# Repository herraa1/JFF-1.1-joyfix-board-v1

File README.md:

# JFF Revision 1.1 JoyFix Board

This is an interposer board that fixes the existing bug in the joystick circuit of the [Just For Fun (JFF) computer revision 1.1](https://github.com/konkotgit/JFF) (up to revision 1.1b) by @skoti.

See the [Omega 1.4 Joyfix Board](https://github.com/herraa1/omega-1.4-joyfix-board-v1) for information on a similar (but not the same) bug affecting the [Omega Home Computer mainboard revision 1.4](https://github.com/skiselev/omega) by Sergey Kiselev.

> [!NOTE]
> This fix is not needed for [JFF 1.1c](https://github.com/konkotgit/JFF?tab=readme-ov-file#revisions), which includes the joystick circuit fix as per [#3](https://github.com/konkotgit/JFF/issues/3).

# The standard MSX joystick circuit

Please, refer to the [details about the standard MSX joystick circuit](https://github.com/herraa1/omega-1.4-joyfix-board-v1?tab=readme-ov-file#the-standard-msx-joystick-circuit) in the [Omega 1.4 Joyfix Board](https://github.com/herraa1/omega-1.4-joyfix-board-v1).

Focusing on the relevant information, output trigger signals must be connected via open-collector buffers like this:
- :white_check_mark: the output at the open-collector buffer corresponding to signal IOB0 is connected to joystick port 1 trigger A
- :white_check_mark: the output at the open-collector buffer corresponding to signal IOB1 is connected to joystick port 1 trigger B
- :white_check_mark: the output at the open-collector buffer corresponding to signal IOB2 is connected to joystick port 2 trigger A
- :white_check_mark: the output at the open-collector buffer corresponding to signal IOB3 is connected to joystick port 2 trigger B

# The JFF 1.1 joystick circuit

As can be seen on the depicted diagram, the JFF PSG circuit tries to mimic the standard MSX joystick circuit, but mixes up the output signals after the open-collector buffers.

If we look closely at the connection of the trigger output signals to the open-collector buffer inputs and the connection of the open-collector buffer outputs to the joystick port signals we can see that:
- :x: the output of the open-collector buffer corresponding to signal IOB0 is incorrectly connected to joystick port 2 trigger B (J2_TR2)
- :x: the output of the open-collector buffer corresponding to signal IOB1 is incorrectly connected to joystick port 2 trigger A (J2_TR1)
- :x: the output of the open-collector buffer corresponding to signal IOB2 is incorrectly connected to joystick port 1 trigger B (J1_TR2)
- :x: the output of the open-collector buffer corresponding to signal IOB3 is incorrectly connected to joystick port 1 trigger A (J1_TR1)

# The fix

The circuit can be easily fixed by re-routing the affected signals to make them available at the right place.

In the JFF 1.1 joystick circuit we have the following connections related to the triggers, taking into account the functional pinout of the [74LS07](https://www.ti.com/lit/ds/symlink/sn74ls07.pdf):
- input `Pin 1` of U20 (connected to IOB0) outputs to `Pin 2` of U20 (incorrectly connected to joystick port 2 trigger B, aka J2_TR2)
- input `Pin 3` of U20 (connected to IOB1) outputs to `Pin 4` of U20 (incorrectly connected to joystick port 2 trigger A, aka J2_TR1)
- input `Pin 5` of U20 (connected to IOB2) outputs to `Pin 6` of U20 (incorrectly connected to joystick port 1 trigger B, aka J1_TR2)
- input `Pin 9` of U20 (connected to IOB3) outputs to `Pin 8` of U20 (incorrectly connected to joystick port 1 trigger A, aka J1_TR1)

A clean and easy approach to fix the circuit is to use an interposer board at U20 (74LS07 open-collector buffer) that performs the needed re-mapping of signals.

So to re-route the signals to match the MSX standard joystick circuit we can map the U20-original signals to a new set of U20-interposed signals (where the 74LS07 will be actually connected), like this:
- Connect `Pin 2 of U20-interposed` (buffered output of Pin 1 of U20-interposed which connects to IOB0) to `Pin 8 of U20-original` (connected to joystick port 1 trigger A, aka J1_TR1), so that Pin 1 of U20-original (IOB0) outputs to Pin 8 of U20-original (joystick port 1 trigger A) ( `violet` path on the diagram)
- Connect `Pin 4 of U20-interposed` (buffered output of Pin 3 of U20-interposed which connects to IOB1) to `Pin 6 of U20-original` (connected to joystick port 1 trigger B, aka J1_TR2), so that Pin 3 of U20-original (IOB1) outputs to Pin 6 of U20-original (joystick port 1 trigger B) ( `green` path on the diagram)
- Connect `Pin 6 of U20-interposed` (buffered output of Pin 5 of U20-interposed which connects to IOB2) to `Pin 4 of U20-original` (connected to joystick port 2 trigger A, aka J2_TR1), so that Pin 5 of U20-original (IOB2) outputs to Pin 4 of U20-original (joystick port 2 trigger A) ( `yellow` path on the diagram)
- Connect `Pin 8 of U20-interposed` (buffered output of Pin 9 of U20-interposed which connects to IOB3) to `Pin 2 of U20-original` (connected to joystick port 2 trigger B, aka J2_TR2), so that Pin 9 of U20-original (IOB3) outputs to Pin 2 of U20-original (joystick port 2 trigger B) ( `orange` path on the diagram)
- Connect all other Pins of U20-interposed to the same Pins of U20-original (i.e Pin 1 to Pin 1, Pin 3 to Pin 3, etc.) ( solid `pink` paths on the diagram)

Summarizing, after the re-routing we have fixed the issue:
- `Pin 1 of U20-original` (connected to IOB0) outputs to `Pin 8 of U20-original` (connected to joystick port 1 trigger A)
- `Pin 3 of U20-original` (connected to IOB1) outputs to `Pin 6 of U20-original` (connected to joystick port 1 trigger B)
- `Pin 5 of U20-original` (connected to IOB2) outputs to `Pin 4 of U20-original` (connected to joystick port 2 trigger A)
- `Pin 9 of U20-original` (connected to IOB3) outputs to `Pin 2 of U20-original` (connected to joystick port 2 trigger B)

And the complete trigger connection diagram matches now the original MSX joystick circuit diagram:
- :white_check_mark: the output at the open-collector buffer corresponding to signal IOB0 is connected to joystick port 1 trigger A (J1_TR1)
- :white_check_mark: the output at the open-collector buffer corresponding to signal IOB1 is connected to joystick port 1 trigger B (J1_TR2)
- :white_check_mark: the output at the open-collector buffer corresponding to signal IOB2 is connected to joystick port 2 trigger A (J2_TR1)
- :white_check_mark: the output at the open-collector buffer corresponding to signal IOB3 is connected to joystick port 2 trigger B (J2_TR2)

# Hardware

## [JFF-joyfix-board-v1-Build1](hardware/kicad/JFF-joyfix-board-v1-Build1/)

:white_check_mark: This board has been successfully built and tested.

[Bill Of Materials (BoM)](https://htmlpreview.github.io/?https://raw.githubusercontent.com/herraa1/JFF-1.1-joyfix-board-v1/main/hardware/kicad/JFF-joyfix-board-v1-Build1/bom/ibom.html)

[Schematic and PCB](https://kicanvas.org/?github=https%3A%2F%2Fgithub.com%2Fherraa1%2FJFF-1.1-joyfix-board-v1%2Ftree%2Fmain%2Fhardware%2Fkicad%2FJFF-joyfix-board-v1-Build1)

## PCB Manufacturing tips

As the joyfix board is super small, some PCB manufacturers may make extra charges when building standalone prototypes or panelizing the boards using v-cuts.

One way to avoid the extra costs is panelizing the joyfix board using "mouse bites".

# Build instructions

Please, follow the [Omega 1.4 Joyfix Board Build Instructions](https://github.com/herraa1/omega-1.4-joyfix-board-v1?tab=readme-ov-file#build-instructions) to assemble the joyfix board. Both boards are assembled using the same procedure.

# Installation instructions

## Step by step instructions

1. Locate the U20 74LS07 IC chip on the JFF computer.

It is a DIP14 IC available near the joystick port 1.

2. Remove the 74LS07 chip from the U20 socket, insert it into the joyfix board socket, and then insert the joyfix board into the U20 socket.

Respect the IC notch markings when orienting both the 74LS07 and the joyfix board for insertion.

Make sure you properly align the joyfix board header pins to the U20 socket to make a good insertion without damaging the U20 socket.

# Validating the fix

Please, refer to the the Omega 1.4 Joyfix Board [Validating the fix](https://github.com/herraa1/omega-1.4-joyfix-board-v1?tab=readme-ov-file#validating-the-fix) section for additional details on how to validate the joyfix board using [MSXJIO](https://github.com/louthrax/MSXJIO) by @Louthrax.

## JFF 1.1 with the joyfix board

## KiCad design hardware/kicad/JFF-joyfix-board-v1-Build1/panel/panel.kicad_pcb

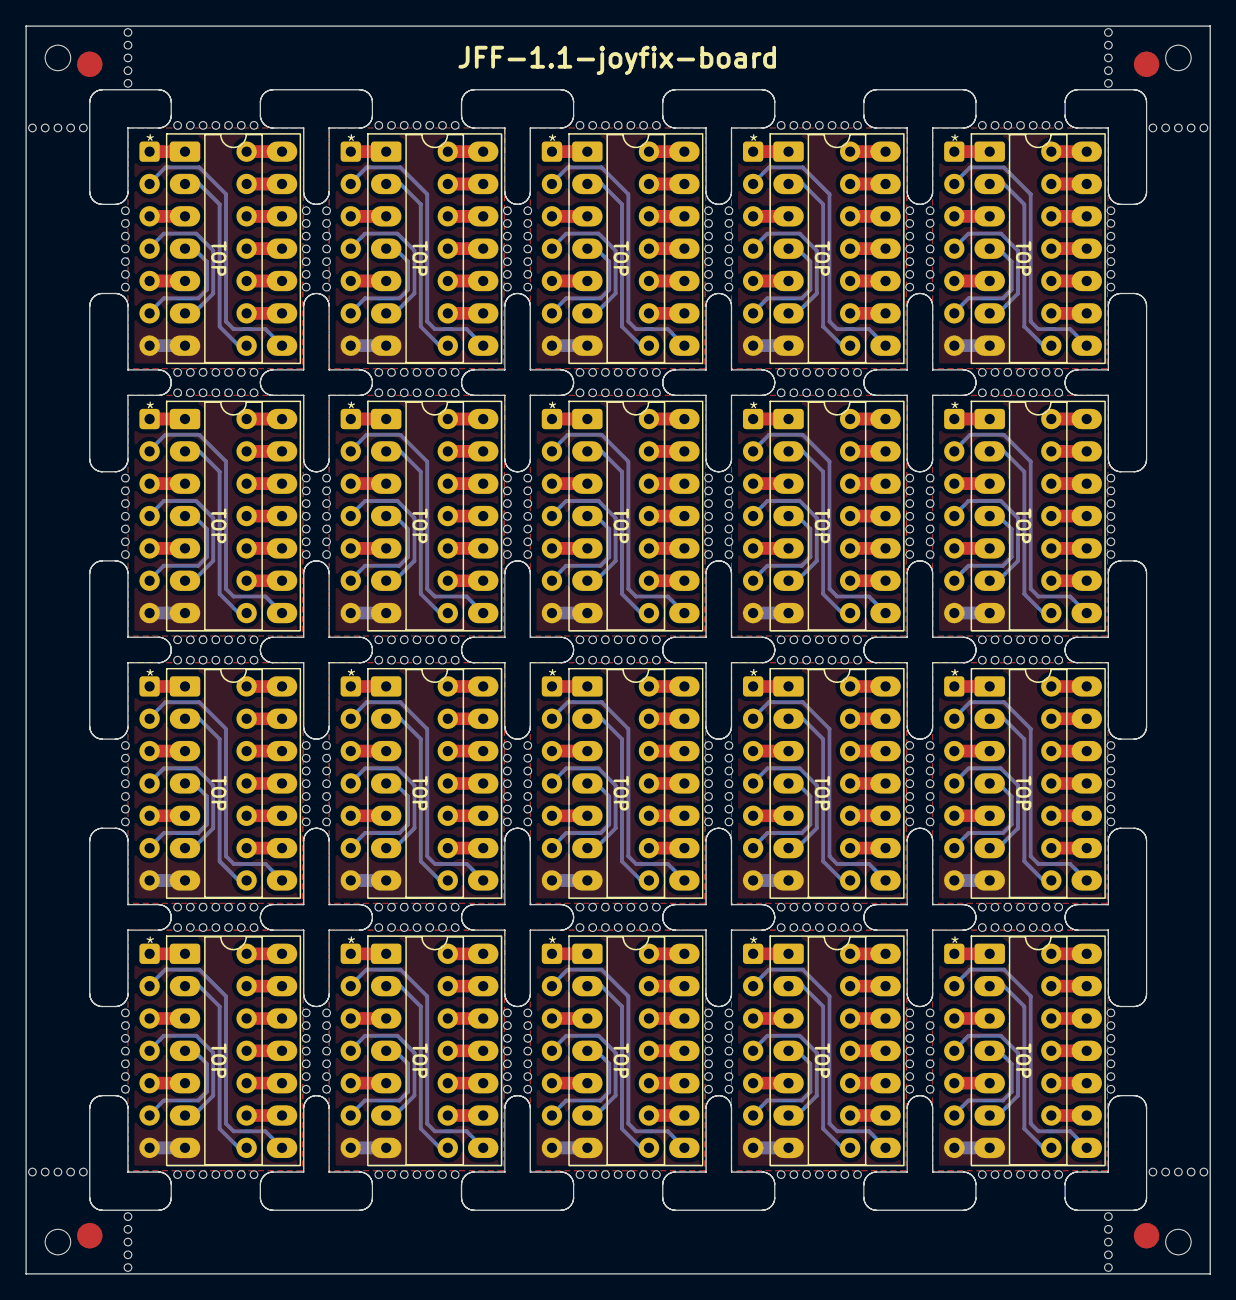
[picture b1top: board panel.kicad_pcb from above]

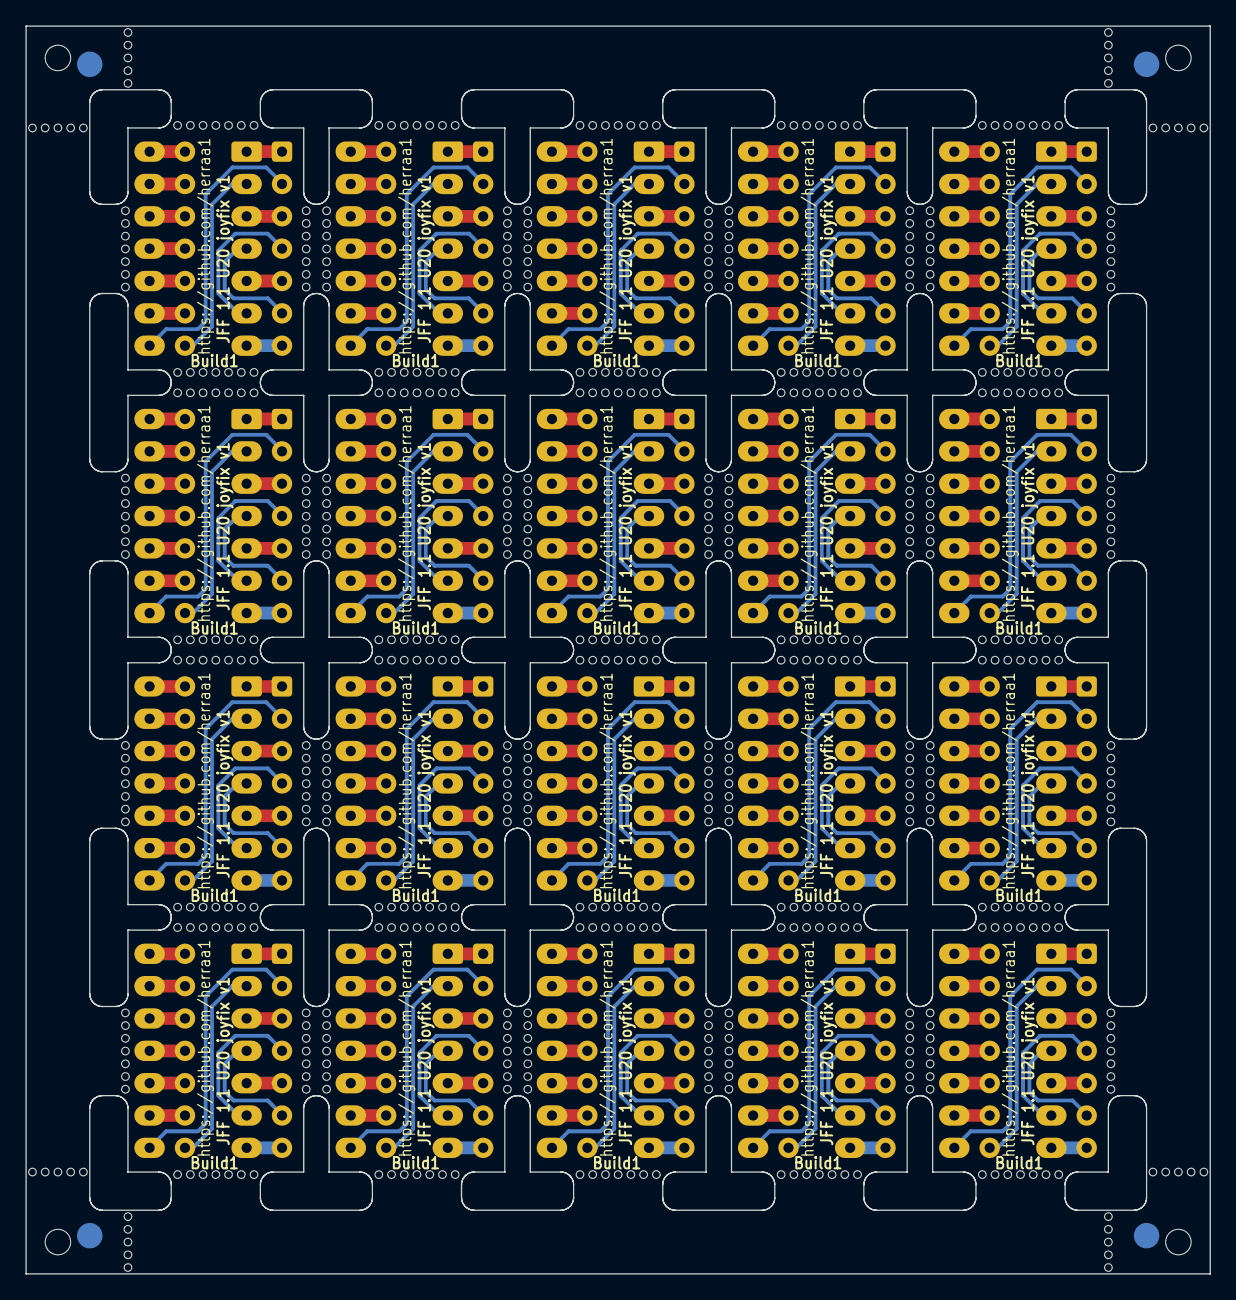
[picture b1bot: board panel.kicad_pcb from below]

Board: 2 copper layers, 93.0 x 98.0 mm, 652 parts (4 on the bottom side), 280 nets.

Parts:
J1, J1#2, J1#3, J1#4, J1#5, J1#6, J1#7, J1#8, J1#9, J1#10, J1#11, J1#12, J1#13, J1#14, J1#15, J1#16, J1#17, J1#18, J1#19, J1#20: To Motherboard; DIP-14_W7.62mm_Socket_Custom
J2, J2#2, J2#3, J2#4, J2#5, J2#6, J2#7, J2#8, J2#9, J2#10, J2#11, J2#12, J2#13, J2#14, J2#15, J2#16, J2#17, J2#18, J2#19, J2#20: To 74LS07; DIP-14_W7.62mm_Socket_LongPads
KiKit_FID_B_1, KiKit_FID_B_2, KiKit_FID_B_3, KiKit_FID_B_4: Fiducial
KiKit_FID_T_1, KiKit_FID_T_2, KiKit_FID_T_3, KiKit_FID_T_4: Fiducial
KiKit_MB_1_2, KiKit_MB_1_3, KiKit_MB_1_4, KiKit_MB_1_5, KiKit_MB_1_6, KiKit_MB_1_7, KiKit_MB_1_8, KiKit_MB_2_2, KiKit_MB_2_3, KiKit_MB_2_4, KiKit_MB_2_5, KiKit_MB_2_6, KiKit_MB_2_7, KiKit_MB_2_8, KiKit_MB_3_2, KiKit_MB_3_3, KiKit_MB_3_4, KiKit_MB_3_5, KiKit_MB_3_6, KiKit_MB_3_7, KiKit_MB_3_8, KiKit_MB_4_2, KiKit_MB_4_3, KiKit_MB_4_4, KiKit_MB_4_5, KiKit_MB_4_6, KiKit_MB_4_7, KiKit_MB_4_8, KiKit_MB_5_2, KiKit_MB_5_3, KiKit_MB_5_4, KiKit_MB_5_5, KiKit_MB_5_6, KiKit_MB_5_7, KiKit_MB_5_8, KiKit_MB_6_2, KiKit_MB_6_3, KiKit_MB_6_4, KiKit_MB_6_5, KiKit_MB_6_6, KiKit_MB_6_7, KiKit_MB_6_8, KiKit_MB_7_2, KiKit_MB_7_3, KiKit_MB_7_4, KiKit_MB_7_5, KiKit_MB_7_6, KiKit_MB_7_7, KiKit_MB_7_8, KiKit_MB_8_2, KiKit_MB_8_3, KiKit_MB_8_4, KiKit_MB_8_5, KiKit_MB_8_6, KiKit_MB_8_7, KiKit_MB_8_8, KiKit_MB_9_2, KiKit_MB_9_3, KiKit_MB_9_4, KiKit_MB_9_5, KiKit_MB_9_6, KiKit_MB_9_7, KiKit_MB_9_8, KiKit_MB_10_2, KiKit_MB_10_3, KiKit_MB_10_4, KiKit_MB_10_5, KiKit_MB_10_6, KiKit_MB_10_7, KiKit_MB_10_8, KiKit_MB_11_2, KiKit_MB_11_3, KiKit_MB_11_4, KiKit_MB_11_5, KiKit_MB_11_6, KiKit_MB_11_7, KiKit_MB_11_8, KiKit_MB_12_2, KiKit_MB_12_3, KiKit_MB_12_4, KiKit_MB_12_5, KiKit_MB_12_6, KiKit_MB_12_7, KiKit_MB_12_8, KiKit_MB_13_2, KiKit_MB_13_3, KiKit_MB_13_4, KiKit_MB_13_5, KiKit_MB_13_6, KiKit_MB_13_7, KiKit_MB_13_8, KiKit_MB_14_2, KiKit_MB_14_3, KiKit_MB_14_4, KiKit_MB_14_5, KiKit_MB_14_6, KiKit_MB_14_7, KiKit_MB_14_8, KiKit_MB_15_2, KiKit_MB_15_3, KiKit_MB_15_4, KiKit_MB_15_5, KiKit_MB_15_6, KiKit_MB_15_7, KiKit_MB_15_8, KiKit_MB_16_2, KiKit_MB_16_3, KiKit_MB_16_4, KiKit_MB_16_5, KiKit_MB_16_6, KiKit_MB_16_7, KiKit_MB_16_8, KiKit_MB_17_2, KiKit_MB_17_3, KiKit_MB_17_4, KiKit_MB_17_5, KiKit_MB_17_6, KiKit_MB_17_7, KiKit_MB_17_8, KiKit_MB_18_2, KiKit_MB_18_3, KiKit_MB_18_4, KiKit_MB_18_5, KiKit_MB_18_6, KiKit_MB_18_7, KiKit_MB_18_8, KiKit_MB_19_2, KiKit_MB_19_3, KiKit_MB_19_4, KiKit_MB_19_5, KiKit_MB_19_6, KiKit_MB_19_7, KiKit_MB_19_8, KiKit_MB_20_2, KiKit_MB_20_3, KiKit_MB_20_4, KiKit_MB_20_5, KiKit_MB_20_6, KiKit_MB_20_7, KiKit_MB_20_8, KiKit_MB_21_2, KiKit_MB_21_3, KiKit_MB_21_4, KiKit_MB_21_5, KiKit_MB_21_6, KiKit_MB_21_7, KiKit_MB_21_8, KiKit_MB_22_2, KiKit_MB_22_3, KiKit_MB_22_4, KiKit_MB_22_5, KiKit_MB_22_6, KiKit_MB_22_7, KiKit_MB_22_8, KiKit_MB_23_2, KiKit_MB_23_3, KiKit_MB_23_4, KiKit_MB_23_5, KiKit_MB_23_6, KiKit_MB_23_7, KiKit_MB_23_8, KiKit_MB_24_2, KiKit_MB_24_3, KiKit_MB_24_4, KiKit_MB_24_5, KiKit_MB_24_6, KiKit_MB_24_7, KiKit_MB_24_8, KiKit_MB_25_2, KiKit_MB_25_3, KiKit_MB_25_4, KiKit_MB_25_5, KiKit_MB_25_6, KiKit_MB_25_7, KiKit_MB_25_8, KiKit_MB_26_2, KiKit_MB_26_3, KiKit_MB_26_4, KiKit_MB_26_5, KiKit_MB_26_6, KiKit_MB_26_7, KiKit_MB_26_8, KiKit_MB_27_2, KiKit_MB_27_3, KiKit_MB_27_4, KiKit_MB_27_5, KiKit_MB_27_6, KiKit_MB_27_7, KiKit_MB_27_8, KiKit_MB_28_2, KiKit_MB_28_3, KiKit_MB_28_4, KiKit_MB_28_5, KiKit_MB_28_6, KiKit_MB_28_7, KiKit_MB_28_8, KiKit_MB_29_2, KiKit_MB_29_3, KiKit_MB_29_4, KiKit_MB_29_5, KiKit_MB_29_6, KiKit_MB_29_7, KiKit_MB_29_8, KiKit_MB_30_2, KiKit_MB_30_3, KiKit_MB_30_4, KiKit_MB_30_5, KiKit_MB_30_6, KiKit_MB_30_7, KiKit_MB_30_8, KiKit_MB_31_2, KiKit_MB_31_3, KiKit_MB_31_4, KiKit_MB_31_5, KiKit_MB_31_6, KiKit_MB_31_7, KiKit_MB_31_8, KiKit_MB_32_2, KiKit_MB_32_3, KiKit_MB_32_4, KiKit_MB_32_5, KiKit_MB_32_6, KiKit_MB_32_7, KiKit_MB_32_8, KiKit_MB_33_2, KiKit_MB_33_3, KiKit_MB_33_4, KiKit_MB_33_5, KiKit_MB_33_6, KiKit_MB_33_7, KiKit_MB_33_8, KiKit_MB_34_2, KiKit_MB_34_3, KiKit_MB_34_4, KiKit_MB_34_5, KiKit_MB_34_6, KiKit_MB_34_7, KiKit_MB_34_8, KiKit_MB_35_2, KiKit_MB_35_3, KiKit_MB_35_4, KiKit_MB_35_5, KiKit_MB_35_6, KiKit_MB_35_7, KiKit_MB_35_8, KiKit_MB_36_2, KiKit_MB_36_3, KiKit_MB_36_4, KiKit_MB_36_5, KiKit_MB_36_6, KiKit_MB_36_7, KiKit_MB_36_8, KiKit_MB_37_2, KiKit_MB_37_3, KiKit_MB_37_4, KiKit_MB_37_5, KiKit_MB_37_6, KiKit_MB_37_7, KiKit_MB_37_8, KiKit_MB_38_2, KiKit_MB_38_3, KiKit_MB_38_4, KiKit_MB_38_5, KiKit_MB_38_6, KiKit_MB_38_7, KiKit_MB_38_8, KiKit_MB_39_2, KiKit_MB_39_3, KiKit_MB_39_4, KiKit_MB_39_5, KiKit_MB_39_6, KiKit_MB_39_7, KiKit_MB_39_8, KiKit_MB_40_2, KiKit_MB_40_3, KiKit_MB_40_4, KiKit_MB_40_5, KiKit_MB_40_6, KiKit_MB_40_7, KiKit_MB_40_8, KiKit_MB_41_2, KiKit_MB_41_3, KiKit_MB_41_4, KiKit_MB_41_5, KiKit_MB_41_6, KiKit_MB_41_7, KiKit_MB_41_8, KiKit_MB_42_2, KiKit_MB_42_3, KiKit_MB_42_4, KiKit_MB_42_5, KiKit_MB_42_6, KiKit_MB_42_7, KiKit_MB_42_8, KiKit_MB_43_2, KiKit_MB_43_3, KiKit_MB_43_4, KiKit_MB_43_5, KiKit_MB_43_6, KiKit_MB_43_7, KiKit_MB_43_8, KiKit_MB_44_2, KiKit_MB_44_3, KiKit_MB_44_4, KiKit_MB_44_5, KiKit_MB_44_6, KiKit_MB_44_7, KiKit_MB_44_8, KiKit_MB_45_2, KiKit_MB_45_3, KiKit_MB_45_4, KiKit_MB_45_5, KiKit_MB_45_6, KiKit_MB_45_7, KiKit_MB_45_8, KiKit_MB_46_2, KiKit_MB_46_3, KiKit_MB_46_4, KiKit_MB_46_5, KiKit_MB_46_6, KiKit_MB_46_7, KiKit_MB_46_8, KiKit_MB_47_2, KiKit_MB_47_3, KiKit_MB_47_4, KiKit_MB_47_5, KiKit_MB_47_6, KiKit_MB_47_7, KiKit_MB_47_8, KiKit_MB_48_2, KiKit_MB_48_3, KiKit_MB_48_4, KiKit_MB_48_5, KiKit_MB_48_6, KiKit_MB_48_7, KiKit_MB_48_8, KiKit_MB_49_2, KiKit_MB_49_3, KiKit_MB_49_4, KiKit_MB_49_5, KiKit_MB_49_6, KiKit_MB_49_7, KiKit_MB_49_8, KiKit_MB_50_2, KiKit_MB_50_3, KiKit_MB_50_4, KiKit_MB_50_5, KiKit_MB_50_6, KiKit_MB_50_7, KiKit_MB_50_8, KiKit_MB_51_2, KiKit_MB_51_3, KiKit_MB_51_4, KiKit_MB_51_5, KiKit_MB_51_6, KiKit_MB_51_7, KiKit_MB_51_8, KiKit_MB_52_2, KiKit_MB_52_3, KiKit_MB_52_4, KiKit_MB_52_5, KiKit_MB_52_6, KiKit_MB_52_7, KiKit_MB_52_8, KiKit_MB_53_2, KiKit_MB_53_3, KiKit_MB_53_4, KiKit_MB_53_5, KiKit_MB_53_6, KiKit_MB_53_7, KiKit_MB_53_8, KiKit_MB_54_2, KiKit_MB_54_3, KiKit_MB_54_4, KiKit_MB_54_5, KiKit_MB_54_6, KiKit_MB_54_7, KiKit_MB_54_8, KiKit_MB_55_2, KiKit_MB_55_3, KiKit_MB_55_4, KiKit_MB_55_5, KiKit_MB_55_6, KiKit_MB_55_7, KiKit_MB_55_8, KiKit_MB_56_2, KiKit_MB_56_3, KiKit_MB_56_4, KiKit_MB_56_5, KiKit_MB_56_6, KiKit_MB_56_7, KiKit_MB_56_8, KiKit_MB_57_2, KiKit_MB_57_3, KiKit_MB_57_4, KiKit_MB_57_5, KiKit_MB_57_6, KiKit_MB_57_7, KiKit_MB_57_8, KiKit_MB_58_2, KiKit_MB_58_3, KiKit_MB_58_4, KiKit_MB_58_5, KiKit_MB_58_6, KiKit_MB_58_7, KiKit_MB_58_8, KiKit_MB_59_2, KiKit_MB_59_3, KiKit_MB_59_4, KiKit_MB_59_5, KiKit_MB_59_6, KiKit_MB_59_7, KiKit_MB_59_8, KiKit_MB_60_2, KiKit_MB_60_3, KiKit_MB_60_4, KiKit_MB_60_5, KiKit_MB_60_6, KiKit_MB_60_7, KiKit_MB_60_8, KiKit_MB_61_2, KiKit_MB_61_3, KiKit_MB_61_4, KiKit_MB_61_5, KiKit_MB_61_6, KiKit_MB_61_7, KiKit_MB_61_8, KiKit_MB_62_2, KiKit_MB_62_3, KiKit_MB_62_4, KiKit_MB_62_5, KiKit_MB_62_6, KiKit_MB_62_7, KiKit_MB_62_8, KiKit_MB_63_2, KiKit_MB_63_3, KiKit_MB_63_4, KiKit_MB_63_5, KiKit_MB_63_6, KiKit_MB_63_7, KiKit_MB_63_8, KiKit_MB_64_2, KiKit_MB_64_3, KiKit_MB_64_4, KiKit_MB_64_5, KiKit_MB_64_6, KiKit_MB_64_7, KiKit_MB_64_8, KiKit_MB_65_2, KiKit_MB_65_3, KiKit_MB_65_4, KiKit_MB_65_5, KiKit_MB_65_6, KiKit_MB_65_7, KiKit_MB_65_8, KiKit_MB_66_2, KiKit_MB_66_3, KiKit_MB_66_4, KiKit_MB_66_5, KiKit_MB_66_6, KiKit_MB_66_7, KiKit_MB_66_8, KiKit_MB_67_2, KiKit_MB_67_3, KiKit_MB_67_4, KiKit_MB_67_5, KiKit_MB_67_6, KiKit_MB_67_7, KiKit_MB_67_8, KiKit_MB_68_2, KiKit_MB_68_3, KiKit_MB_68_4, KiKit_MB_68_5, KiKit_MB_68_6, KiKit_MB_68_7, KiKit_MB_68_8, KiKit_MB_69_2, KiKit_MB_69_3, KiKit_MB_69_4, KiKit_MB_69_5, KiKit_MB_69_6, KiKit_MB_69_7, KiKit_MB_69_8, KiKit_MB_70_2, KiKit_MB_70_3, KiKit_MB_70_4, KiKit_MB_70_5, KiKit_MB_70_6, KiKit_MB_70_7, KiKit_MB_70_8, KiKit_MB_71_2, KiKit_MB_71_3, KiKit_MB_71_4, KiKit_MB_71_5, KiKit_MB_71_6, KiKit_MB_71_7, KiKit_MB_71_8, KiKit_MB_72_2, KiKit_MB_72_3, KiKit_MB_72_4, KiKit_MB_72_5, KiKit_MB_72_6, KiKit_MB_72_7, KiKit_MB_72_8, KiKit_MB_73_2, KiKit_MB_73_3, KiKit_MB_73_4, KiKit_MB_73_5, KiKit_MB_73_6, KiKit_MB_73_7, KiKit_MB_73_8, KiKit_MB_74_2, KiKit_MB_74_3, KiKit_MB_74_4, KiKit_MB_74_5, KiKit_MB_74_6, KiKit_MB_74_7, KiKit_MB_74_8, KiKit_MB_75_2, KiKit_MB_75_3, KiKit_MB_75_4, KiKit_MB_75_5, KiKit_MB_75_6, KiKit_MB_75_7, KiKit_MB_75_8, KiKit_MB_76_2, KiKit_MB_76_3, KiKit_MB_76_4, KiKit_MB_76_5, KiKit_MB_76_6, KiKit_MB_76_7, KiKit_MB_76_8, KiKit_MB_77_2, KiKit_MB_77_3, KiKit_MB_77_4, KiKit_MB_77_5, KiKit_MB_77_6, KiKit_MB_77_7, KiKit_MB_77_8, KiKit_MB_78_2, KiKit_MB_78_3, KiKit_MB_78_4, KiKit_MB_78_5, KiKit_MB_78_6, KiKit_MB_78_7, KiKit_MB_78_8, KiKit_MB_79_2, KiKit_MB_79_3, KiKit_MB_79_4, KiKit_MB_79_5, KiKit_MB_79_6, KiKit_MB_79_7, KiKit_MB_79_8, KiKit_MB_80_2, KiKit_MB_80_3, KiKit_MB_80_4, KiKit_MB_80_5, KiKit_MB_80_6, KiKit_MB_80_7, KiKit_MB_80_8, KiKit_MB_81_2, KiKit_MB_81_3, KiKit_MB_81_4, KiKit_MB_81_5, KiKit_MB_81_6, KiKit_MB_82_2, KiKit_MB_82_3, KiKit_MB_82_4, KiKit_MB_82_5, KiKit_MB_82_6, KiKit_MB_83_2, KiKit_MB_83_3, KiKit_MB_83_4, KiKit_MB_83_5, KiKit_MB_83_6, KiKit_MB_84_2, KiKit_MB_84_3, KiKit_MB_84_4, KiKit_MB_84_5, KiKit_MB_84_6, KiKit_MB_85_2, KiKit_MB_85_3, KiKit_MB_85_4, KiKit_MB_85_5, KiKit_MB_85_6, KiKit_MB_86_2, KiKit_MB_86_3, KiKit_MB_86_4, KiKit_MB_86_5, KiKit_MB_86_6, KiKit_MB_87_2, KiKit_MB_87_3, KiKit_MB_87_4, KiKit_MB_87_5, KiKit_MB_87_6, KiKit_MB_88_2, KiKit_MB_88_3, KiKit_MB_88_4, KiKit_MB_88_5, KiKit_MB_88_6: NPTH
KiKit_TO_1, KiKit_TO_2, KiKit_TO_3, KiKit_TO_4: NPTH

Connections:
Board_0-/GND: J1#14.7, J2#19.7
Board_0-/IOB0: J1#14.1, J2#19.1
Board_0-/IOB1: J1#14.3, J2#19.3
Board_0-/IOB2: J1#14.5, J2#19.5
Board_0-/IOB3: J1#14.9, J2#19.9
Board_0-/J1TRG1: J1#14.8, J2#19.2
Board_0-/J1TRG2: J1#14.6, J2#19.4
Board_0-/J2TRG1: J1#14.4, J2#19.6
Board_0-/J2TRG2: J1#14.2, J2#19.8
Board_0-/VCC: J1#14.14, J2#19.14
Board_0-Net-(J1-Pin_10): J1#14.10, J2#19.10
Board_0-Net-(J1-Pin_11): J1#14.11, J2#19.11
Board_0-Net-(J1-Pin_12): J1#14.12, J2#19.12
Board_0-Net-(J1-Pin_13): J1#14.13, J2#19.13
Board_1-/GND: J1#16.7, J2#20.7
Board_1-/IOB0: J1#16.1, J2#20.1
Board_1-/IOB1: J1#16.3, J2#20.3
Board_1-/IOB2: J1#16.5, J2#20.5
Board_1-/IOB3: J1#16.9, J2#20.9
Board_1-/J1TRG1: J1#16.8, J2#20.2
Board_1-/J1TRG2: J1#16.6, J2#20.4
Board_1-/J2TRG1: J1#16.4, J2#20.6
Board_1-/J2TRG2: J1#16.2, J2#20.8
Board_1-/VCC: J1#16.14, J2#20.14
Board_1-Net-(J1-Pin_10): J1#16.10, J2#20.10
Board_1-Net-(J1-Pin_11): J1#16.11, J2#20.11
Board_1-Net-(J1-Pin_12): J1#16.12, J2#20.12
Board_1-Net-(J1-Pin_13): J1#16.13, J2#20.13
Board_2-/GND: J1#12.7, J2#11.7
Board_2-/IOB0: J1#12.1, J2#11.1
Board_2-/IOB1: J1#12.3, J2#11.3
Board_2-/IOB2: J1#12.5, J2#11.5
Board_2-/IOB3: J1#12.9, J2#11.9
Board_2-/J1TRG1: J1#12.8, J2#11.2
Board_2-/J1TRG2: J1#12.6, J2#11.4
Board_2-/J2TRG1: J1#12.4, J2#11.6
Board_2-/J2TRG2: J1#12.2, J2#11.8
Board_2-/VCC: J1#12.14, J2#11.14
Board_2-Net-(J1-Pin_10): J1#12.10, J2#11.10
Board_2-Net-(J1-Pin_11): J1#12.11, J2#11.11
Board_2-Net-(J1-Pin_12): J1#12.12, J2#11.12
Board_2-Net-(J1-Pin_13): J1#12.13, J2#11.13
Board_3-/GND: J1#17.7, J2#5.7
Board_3-/IOB0: J1#17.1, J2#5.1
Board_3-/IOB1: J1#17.3, J2#5.3
Board_3-/IOB2: J1#17.5, J2#5.5
Board_3-/IOB3: J1#17.9, J2#5.9
Board_3-/J1TRG1: J1#17.8, J2#5.2
Board_3-/J1TRG2: J1#17.6, J2#5.4
Board_3-/J2TRG1: J1#17.4, J2#5.6
Board_3-/J2TRG2: J1#17.2, J2#5.8
Board_3-/VCC: J1#17.14, J2#5.14
Board_3-Net-(J1-Pin_10): J1#17.10, J2#5.10
Board_3-Net-(J1-Pin_11): J1#17.11, J2#5.11
Board_3-Net-(J1-Pin_12): J1#17.12, J2#5.12
Board_3-Net-(J1-Pin_13): J1#17.13, J2#5.13
Board_4-/GND: J1#13.7, J2#16.7
Board_4-/IOB0: J1#13.1, J2#16.1
Board_4-/IOB1: J1#13.3, J2#16.3
Board_4-/IOB2: J1#13.5, J2#16.5
Board_4-/IOB3: J1#13.9, J2#16.9
Board_4-/J1TRG1: J1#13.8, J2#16.2
Board_4-/J1TRG2: J1#13.6, J2#16.4
Board_4-/J2TRG1: J1#13.4, J2#16.6
Board_4-/J2TRG2: J1#13.2, J2#16.8
Board_4-/VCC: J1#13.14, J2#16.14
Board_4-Net-(J1-Pin_10): J1#13.10, J2#16.10
Board_4-Net-(J1-Pin_11): J1#13.11, J2#16.11
Board_4-Net-(J1-Pin_12): J1#13.12, J2#16.12
Board_4-Net-(J1-Pin_13): J1#13.13, J2#16.13
Board_5-/GND: J1#15.7, J2#10.7
Board_5-/IOB0: J1#15.1, J2#10.1
Board_5-/IOB1: J1#15.3, J2#10.3
Board_5-/IOB2: J1#15.5, J2#10.5
Board_5-/IOB3: J1#15.9, J2#10.9
Board_5-/J1TRG1: J1#15.8, J2#10.2
Board_5-/J1TRG2: J1#15.6, J2#10.4
Board_5-/J2TRG1: J1#15.4, J2#10.6
Board_5-/J2TRG2: J1#15.2, J2#10.8
Board_5-/VCC: J1#15.14, J2#10.14
Board_5-Net-(J1-Pin_10): J1#15.10, J2#10.10
Board_5-Net-(J1-Pin_11): J1#15.11, J2#10.11
Board_5-Net-(J1-Pin_12): J1#15.12, J2#10.12
Board_5-Net-(J1-Pin_13): J1#15.13, J2#10.13
Board_6-/GND: J1#6.7, J2#6.7
Board_6-/IOB0: J1#6.1, J2#6.1
Board_6-/IOB1: J1#6.3, J2#6.3
Board_6-/IOB2: J1#6.5, J2#6.5
Board_6-/IOB3: J1#6.9, J2#6.9
Board_6-/J1TRG1: J1#6.8, J2#6.2
Board_6-/J1TRG2: J1#6.6, J2#6.4
Board_6-/J2TRG1: J1#6.4, J2#6.6
Board_6-/J2TRG2: J1#6.2, J2#6.8
Board_6-/VCC: J1#6.14, J2#6.14
Board_6-Net-(J1-Pin_10): J1#6.10, J2#6.10
Board_6-Net-(J1-Pin_11): J1#6.11, J2#6.11
Board_6-Net-(J1-Pin_12): J1#6.12, J2#6.12
Board_6-Net-(J1-Pin_13): J1#6.13, J2#6.13
Board_7-/GND: J1#11.7, J2#9.7
Board_7-/IOB0: J1#11.1, J2#9.1
Board_7-/IOB1: J1#11.3, J2#9.3
Board_7-/IOB2: J1#11.5, J2#9.5
Board_7-/IOB3: J1#11.9, J2#9.9
Board_7-/J1TRG1: J1#11.8, J2#9.2
Board_7-/J1TRG2: J1#11.6, J2#9.4
Board_7-/J2TRG1: J1#11.4, J2#9.6
Board_7-/J2TRG2: J1#11.2, J2#9.8
Board_7-/VCC: J1#11.14, J2#9.14
Board_7-Net-(J1-Pin_10): J1#11.10, J2#9.10
Board_7-Net-(J1-Pin_11): J1#11.11, J2#9.11
Board_7-Net-(J1-Pin_12): J1#11.12, J2#9.12
Board_7-Net-(J1-Pin_13): J1#11.13, J2#9.13
Board_8-/GND: J1#2.7, J2#14.7
Board_8-/IOB0: J1#2.1, J2#14.1
Board_8-/IOB1: J1#2.3, J2#14.3
Board_8-/IOB2: J1#2.5, J2#14.5
Board_8-/IOB3: J1#2.9, J2#14.9
Board_8-/J1TRG1: J1#2.8, J2#14.2
Board_8-/J1TRG2: J1#2.6, J2#14.4
Board_8-/J2TRG1: J1#2.4, J2#14.6
Board_8-/J2TRG2: J1#2.2, J2#14.8
Board_8-/VCC: J1#2.14, J2#14.14
Board_8-Net-(J1-Pin_10): J1#2.10, J2#14.10
Board_8-Net-(J1-Pin_11): J1#2.11, J2#14.11
Board_8-Net-(J1-Pin_12): J1#2.12, J2#14.12
Board_8-Net-(J1-Pin_13): J1#2.13, J2#14.13
Board_9-/GND: J1#7.7, J2#2.7
Board_9-/IOB0: J1#7.1, J2#2.1
Board_9-/IOB1: J1#7.3, J2#2.3
Board_9-/IOB2: J1#7.5, J2#2.5
Board_9-/IOB3: J1#7.9, J2#2.9
Board_9-/J1TRG1: J1#7.8, J2#2.2
Board_9-/J1TRG2: J1#7.6, J2#2.4
Board_9-/J2TRG1: J1#7.4, J2#2.6
Board_9-/J2TRG2: J1#7.2, J2#2.8
Board_9-/VCC: J1#7.14, J2#2.14
Board_9-Net-(J1-Pin_10): J1#7.10, J2#2.10
Board_9-Net-(J1-Pin_11): J1#7.11, J2#2.11
Board_9-Net-(J1-Pin_12): J1#7.12, J2#2.12
Board_9-Net-(J1-Pin_13): J1#7.13, J2#2.13
Board_10-/GND: J1.7, J2#8.7
Board_10-/IOB0: J1.1, J2#8.1
Board_10-/IOB1: J1.3, J2#8.3
Board_10-/IOB2: J1.5, J2#8.5
Board_10-/IOB3: J1.9, J2#8.9
Board_10-/J1TRG1: J1.8, J2#8.2
Board_10-/J1TRG2: J1.6, J2#8.4
Board_10-/J2TRG1: J1.4, J2#8.6
Board_10-/J2TRG2: J1.2, J2#8.8
Board_10-/VCC: J1.14, J2#8.14
Board_10-Net-(J1-Pin_10): J1.10, J2#8.10
Board_10-Net-(J1-Pin_11): J1.11, J2#8.11
Board_10-Net-(J1-Pin_12): J1.12, J2#8.12
Board_10-Net-(J1-Pin_13): J1.13, J2#8.13
Board_11-/GND: J1#4.7, J2#15.7
Board_11-/IOB0: J1#4.1, J2#15.1
Board_11-/IOB1: J1#4.3, J2#15.3
Board_11-/IOB2: J1#4.5, J2#15.5
Board_11-/IOB3: J1#4.9, J2#15.9
Board_11-/J1TRG1: J1#4.8, J2#15.2
Board_11-/J1TRG2: J1#4.6, J2#15.4
Board_11-/J2TRG1: J1#4.4, J2#15.6
Board_11-/J2TRG2: J1#4.2, J2#15.8
Board_11-/VCC: J1#4.14, J2#15.14
Board_11-Net-(J1-Pin_10): J1#4.10, J2#15.10
Board_11-Net-(J1-Pin_11): J1#4.11, J2#15.11
Board_11-Net-(J1-Pin_12): J1#4.12, J2#15.12
Board_11-Net-(J1-Pin_13): J1#4.13, J2#15.13
Board_12-/GND: J1#5.7, J2#18.7
Board_12-/IOB0: J1#5.1, J2#18.1
Board_12-/IOB1: J1#5.3, J2#18.3
Board_12-/IOB2: J1#5.5, J2#18.5
Board_12-/IOB3: J1#5.9, J2#18.9
Board_12-/J1TRG1: J1#5.8, J2#18.2
Board_12-/J1TRG2: J1#5.6, J2#18.4
Board_12-/J2TRG1: J1#5.4, J2#18.6
Board_12-/J2TRG2: J1#5.2, J2#18.8
Board_12-/VCC: J1#5.14, J2#18.14
Board_12-Net-(J1-Pin_10): J1#5.10, J2#18.10
Board_12-Net-(J1-Pin_11): J1#5.11, J2#18.11
Board_12-Net-(J1-Pin_12): J1#5.12, J2#18.12
Board_12-Net-(J1-Pin_13): J1#5.13, J2#18.13
Board_13-/GND: J1#9.7, J2.7
Board_13-/IOB0: J1#9.1, J2.1
Board_13-/IOB1: J1#9.3, J2.3
Board_13-/IOB2: J1#9.5, J2.5
Board_13-/IOB3: J1#9.9, J2.9
Board_13-/J1TRG1: J1#9.8, J2.2
Board_13-/J1TRG2: J1#9.6, J2.4
Board_13-/J2TRG1: J1#9.4, J2.6
Board_13-/J2TRG2: J1#9.2, J2.8
Board_13-/VCC: J1#9.14, J2.14
Board_13-Net-(J1-Pin_10): J1#9.10, J2.10
Board_13-Net-(J1-Pin_11): J1#9.11, J2.11
Board_13-Net-(J1-Pin_12): J1#9.12, J2.12
Board_13-Net-(J1-Pin_13): J1#9.13, J2.13
Board_14-/GND: J1#18.7, J2#12.7
Board_14-/IOB0: J1#18.1, J2#12.1
Board_14-/IOB1: J1#18.3, J2#12.3
Board_14-/IOB2: J1#18.5, J2#12.5
Board_14-/IOB3: J1#18.9, J2#12.9
Board_14-/J1TRG1: J1#18.8, J2#12.2
Board_14-/J1TRG2: J1#18.6, J2#12.4
Board_14-/J2TRG1: J1#18.4, J2#12.6
Board_14-/J2TRG2: J1#18.2, J2#12.8
Board_14-/VCC: J1#18.14, J2#12.14
Board_14-Net-(J1-Pin_10): J1#18.10, J2#12.10
Board_14-Net-(J1-Pin_11): J1#18.11, J2#12.11
Board_14-Net-(J1-Pin_12): J1#18.12, J2#12.12
Board_14-Net-(J1-Pin_13): J1#18.13, J2#12.13
Board_15-/GND: J1#3.7, J2#3.7
Board_15-/IOB0: J1#3.1, J2#3.1
Board_15-/IOB1: J1#3.3, J2#3.3
Board_15-/IOB2: J1#3.5, J2#3.5
Board_15-/IOB3: J1#3.9, J2#3.9
Board_15-/J1TRG1: J1#3.8, J2#3.2
Board_15-/J1TRG2: J1#3.6, J2#3.4
Board_15-/J2TRG1: J1#3.4, J2#3.6
Board_15-/J2TRG2: J1#3.2, J2#3.8
Board_15-/VCC: J1#3.14, J2#3.14
Board_15-Net-(J1-Pin_10): J1#3.10, J2#3.10
Board_15-Net-(J1-Pin_11): J1#3.11, J2#3.11
Board_15-Net-(J1-Pin_12): J1#3.12, J2#3.12
Board_15-Net-(J1-Pin_13): J1#3.13, J2#3.13
Board_16-/GND: J1#8.7, J2#13.7
Board_16-/IOB0: J1#8.1, J2#13.1
Board_16-/IOB1: J1#8.3, J2#13.3
Board_16-/IOB2: J1#8.5, J2#13.5
Board_16-/IOB3: J1#8.9, J2#13.9
Board_16-/J1TRG1: J1#8.8, J2#13.2
Board_16-/J1TRG2: J1#8.6, J2#13.4
Board_16-/J2TRG1: J1#8.4, J2#13.6
Board_16-/J2TRG2: J1#8.2, J2#13.8
Board_16-/VCC: J1#8.14, J2#13.14
Board_16-Net-(J1-Pin_10): J1#8.10, J2#13.10
Board_16-Net-(J1-Pin_11): J1#8.11, J2#13.11
Board_16-Net-(J1-Pin_12): J1#8.12, J2#13.12
Board_16-Net-(J1-Pin_13): J1#8.13, J2#13.13
Board_17-/GND: J1#10.7, J2#7.7
Board_17-/IOB0: J1#10.1, J2#7.1
Board_17-/IOB1: J1#10.3, J2#7.3
Board_17-/IOB2: J1#10.5, J2#7.5
Board_17-/IOB3: J1#10.9, J2#7.9
Board_17-/J1TRG1: J1#10.8, J2#7.2
Board_17-/J1TRG2: J1#10.6, J2#7.4
Board_17-/J2TRG1: J1#10.4, J2#7.6
Board_17-/J2TRG2: J1#10.2, J2#7.8
Board_17-/VCC: J1#10.14, J2#7.14
Board_17-Net-(J1-Pin_10): J1#10.10, J2#7.10
Board_17-Net-(J1-Pin_11): J1#10.11, J2#7.11
Board_17-Net-(J1-Pin_12): J1#10.12, J2#7.12
Board_17-Net-(J1-Pin_13): J1#10.13, J2#7.13
Board_18-/GND: J1#19.7, J2#17.7
Board_18-/IOB0: J1#19.1, J2#17.1
Board_18-/IOB1: J1#19.3, J2#17.3
Board_18-/IOB2: J1#19.5, J2#17.5
Board_18-/IOB3: J1#19.9, J2#17.9
Board_18-/J1TRG1: J1#19.8, J2#17.2
Board_18-/J1TRG2: J1#19.6, J2#17.4
Board_18-/J2TRG1: J1#19.4, J2#17.6
Board_18-/J2TRG2: J1#19.2, J2#17.8
Board_18-/VCC: J1#19.14, J2#17.14
Board_18-Net-(J1-Pin_10): J1#19.10, J2#17.10
Board_18-Net-(J1-Pin_11): J1#19.11, J2#17.11
Board_18-Net-(J1-Pin_12): J1#19.12, J2#17.12
Board_18-Net-(J1-Pin_13): J1#19.13, J2#17.13
Board_19-/GND: J1#20.7, J2#4.7
Board_19-/IOB0: J1#20.1, J2#4.1
Board_19-/IOB1: J1#20.3, J2#4.3
Board_19-/IOB2: J1#20.5, J2#4.5
Board_19-/IOB3: J1#20.9, J2#4.9
Board_19-/J1TRG1: J1#20.8, J2#4.2
Board_19-/J1TRG2: J1#20.6, J2#4.4
Board_19-/J2TRG1: J1#20.4, J2#4.6
Board_19-/J2TRG2: J1#20.2, J2#4.8
Board_19-/VCC: J1#20.14, J2#4.14
Board_19-Net-(J1-Pin_10): J1#20.10, J2#4.10
Board_19-Net-(J1-Pin_11): J1#20.11, J2#4.11
Board_19-Net-(J1-Pin_12): J1#20.12, J2#4.12
Board_19-Net-(J1-Pin_13): J1#20.13, J2#4.13

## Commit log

2025-10-04 Initial commit.
2025-10-04 kicad: added missing ibom
2025-10-04 readme: fix wrong IC reference in image
2025-10-06 readme: add note about new JFF 1.1c version which fixes the joystick bug
2026-02-27 fix htmlpreview link
